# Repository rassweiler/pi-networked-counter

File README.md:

# pi-networked-counter
Network attached counter using Pi5, python, pyqt6, and sqlite

## Dev Setup (Linux)

- clone repository:
```
git clone https://github.com/rassweiler/pi-networked-counter.git && cd pi-networked-counter
```

- Setup python environment:
```
python3 -m venv venv

source venv/bin/activate

pip3 install gpiozero lgpio msal msal_extensions python-dotenv pygobject
```

- Install optional packages:
```
sudo apt install qtcreator sqlitebrowser
```

## Device Setup (Pi5+)

### Base Version Part List
- 1 [Raspberry Pi 5+](https://www.canakit.com/raspberry-pi-5-8gb.html?cid=CAD&src=raspberrypi)
- 1 [Raspberry Pi 5+ Power Supply](https://www.canakit.com/official-raspberry-pi-5-power-supply-27w-usb-c.html?defpid=4863)
- 1 [Micro SSD](https://www.amazon.ca/Samsung-Memory-Adapter-Limited-Warranty/dp/B09FFD6R2B/)
- 1 [Raspberry Pi 7" screen](https://www.canakit.com/raspberry-pi-lcd-display-touchscreen.html)
- 1 [Pi5 Diplay adapter cable](https://www.canakit.com/raspberry-pi-5-display-cable.html)
- 2 [Harting Cables](https://www.digikey.ca/en/products/detail/harting/21350102507010/16669171)
- 2 [M12 AMP Connector Male](https://www.digikey.ca/en/products/detail/te-connectivity-amp-connectors/T4171010005-001/7927449)
- 2 [M12 AMP Connector Female](https://www.digikey.ca/en/products/detail/te-connectivity-amp-connectors/T4171110005-001/7221411)
- 1 [Pack of jumper pin connectors](https://www.amazon.ca/Elegoo-120pcs-Multicolored-Breadboard-arduino/dp/B01EV70C78/)
- 1 [Roll of PETG filament](https://www.prusa3d.com/product/prusament-petg-anthracite-grey-1kg/)
- 2 [IR Emitter/ Receiver 5mm 3.3v](https://www.adafruit.com/product/2168#technical-details)
- 1 [Ethernet Keystone Inline](https://www.amazon.ca/5PACK-CAT6-Keystone-Inline-Coupler-White/dp/B0116T7XMQ/)
- 1 [Ethernet Patch Cable](https://www.amazon.ca/Cat-Ethernet-Cable-0-5ft-Pack/dp/B0CMQG7GS1)
- 1 [USB C Keystone Jack Adapter USB 3.1](https://www.amazon.ca/AAOTOKK-Keystone-Adapter-Type-C-Coupler/dp/B07Z947FRN)
- 1 [USB C patch cable](https://www.amazon.ca/Silkland-Charging-Compatible-MacBook-Samsung/dp/B0CQ4SX256)
- 1 [USB A Keystone Jack Cable](https://www.amazon.ca/Keystone-Haokiang-Adapters-Connector-Cable-20CM/dp/B07JFRLLQF)
- 1 [22awg Wire 2 Conductor 25ft](https://www.digikey.ca/en/products/detail/prysmian/C6348A-46-10/2761061)
- 1 [Rugged Metal Pushbutton - 16mm White Momentary](https://www.adafruit.com/product/558)
- 2 [Wire Connector Pack](https://www.amazon.ca/Connector-Solderless-Connectors-Stripping-Electrical/dp/B08929GXGK)
- 1 [GPIO Ribbon Cable](https://www.adafruit.com/product/1988)
- 1 [GPIO Header](https://www.pishop.ca/product/40-pin-gpio-connector-header/)

### Stacklight Version Part List
- 1 [DC Power Panel Jack](https://www.amazon.ca/DIYhz-Socket-Female-Mounting-Connector/dp/B079D6P26P)
- 1 [DC Power Supply](https://www.amazon.ca/ALITOVE-Adapter-Converter-100-240V-5-5x2-1mm/dp/B01GEA8PQA)
- 1 [Through-Hole Resistors - 1K ohm 5% 1/4W](https://www.adafruit.com/product/4294)
- 1 [Through-Hole Resistors - 220 ohm 5% 1/4W](https://www.adafruit.com/product/2780)
- 1 [AQY210EH SSR](https://www.digikey.ca/en/products/detail/panasonic-electric-works/AQY210EH/513082)
- 1 [Tower Light - Red Yellow Green Alert Light](https://www.adafruit.com/product/2993#technical-details)
- 1 [Tiny Premium Breadboard](https://www.adafruit.com/product/65#description)

### Optional Parts
- 1 [Pi5 POE Hat](https://www.pishop.ca/product/power-over-ethernet-hat-f-for-raspberry-pi-5-cooling-fan-802-3af-at/)

### Pi Software

- Update system
```
sudo apt update && sudo apt upgrade
```

- Install packages
```
sudo apt install < .packages
```

- Disable sudo NOPASSWD:
```
sudo nano /etc/sudoers.d/010_pi-nopasswd

remove NOPASSWD:
```

- Enable sudo logging:
```
sudo visudo

Insert:

Defaults    logfile=/var/log/sudo
```

- Harden ssh config:
```
sudo nano /etc/ssh/sshd_config

PermitRootLogin prohibit-password
MaxAuthTries 5
MaxSessions 3
MaxStartups 3:90:15
PasswordAuthentication no
```

- Harden ssh keys:
```
echo -e "# Restrict key exchange, cipher, and MAC algorithms, as per sshaudit.com\n# hardening guide.\n KexAlgorithms sntrup761x25519-sha512,sntrup761x25519-sha512@openssh.com,curve25519-sha256,curve25519-sha256@libssh.org,gss-curve25519-sha256-,diffie-hellman-group16-sha512,gss-group16-sha512-,diffie-hellman-group18-sha512,diffie-hellman-group-exchange-sha256\n\nCiphers chacha20-poly1305@openssh.com,aes256-gcm@openssh.com,aes256-ctr,aes192-ctr,aes128-gcm@openssh.com,aes128-ctr\n\nMACs hmac-sha2-256-etm@openssh.com,hmac-sha2-512-etm@openssh.com,umac-128-etm@openssh.com\n\nHostKeyAlgorithms sk-ssh-ed25519-cert-v01@openssh.com,ssh-ed25519-cert-v01@openssh.com,rsa-sha2-512-cert-v01@openssh.com,rsa-sha2-256-cert-v01@openssh.com,sk-ssh-ed25519@openssh.com,ssh-ed25519,rsa-sha2-512,rsa-sha2-256\n\nRequiredRSASize 3072\n\nCASignatureAlgorithms sk-ssh-ed25519@openssh.com,ssh-ed25519,rsa-sha2-512,rsa-sha2-256\n\nGSSAPIKexAlgorithms gss-curve25519-sha256-,gss-group16-sha512-\n\nHostbasedAcceptedAlgorithms sk-ssh-ed25519-cert-v01@openssh.com,ssh-ed25519-cert-v01@openssh.com,sk-ssh-ed25519@openssh.com,ssh-ed25519,rsa-sha2-512-cert-v01@openssh.com,rsa-sha2-512,rsa-sha2-256-cert-v01@openssh.com,rsa-sha2-256\n\nPubkeyAcceptedAlgorithms sk-ssh-ed25519-cert-v01@openssh.com,ssh-ed25519-cert-v01@openssh.com,sk-ssh-ed25519@openssh.com,ssh-ed25519,rsa-sha2-512-cert-v01@openssh.com,rsa-sha2-512,rsa-sha2-256-cert-v01@openssh.com,rsa-sha2-256\n\n" > /etc/ssh/sshd_config.d/ssh-audit_hardening.conf
```

- Remove avahi:
```
sudo systemctl stop avahi-daemon && sudo systemctl disable avahi-daemon

sudo apt purge avahi-daemon -y
```

- Remove CUPS:
```
sudo systemctl stop cups && sudo systemctl disable cups

sudo apt purge cups -y 
```

- PI configure
Set the locale to UTF-8

- Setup keyring for sharepoint integration
Run seahorse and make sure there is a default keystore

- clone repository to PI:
```
git clone https://github.com/rassweiler/pi-networked-counter.git && cd pi-networked-counter
```

- Copy the desktop file to autostart the app:
```
sudo cp objectcounter.desktop /etc/xdg/autostart/objectcounter.desktop
```

- Add panel icon
```
cp objectcounter.desktop ~/.local/share/applications/
```

Then restart the system to get the app in the menu under other, then right click the app and select add to taskbar

- Setup startup IO for push button
```
echo "dtoverlay=gpio-poweroff,gpiopin=25,active_low" >> /boot/firmware/config.txt
```

### Sharepoint Setup (Optional)

- Add to the `.settup.toml` file your sharepoint access details:
```
[sharepoint]
authority = "https://login.microsoftonline.com/{AID}"
client = "{CID}"
scopes = 'User.ReadBasic.All Files.ReadWrite Sites.ReadWrite.All'
endpoint = "https://graph.microsoft.com/v1.0/me" 
```

- run the `get_token.sh` script once to initialise your sharepoint token, it should provide a link and a key to login using a browser.

### Print Parts

- Print out the [Front case](./Models/Exports/NetworkCounter_Case_Front_Print.3mf) section (Should contain the screen brackets as well)
- Print out the [Rear case](./Models/Exports/NetworkCounter_Case_Back_Print.3mf) section
- Print out the [Sensor case](./Models/Exports/NetworkCounter_SensorCase_Front_Print.3mf) sections
- Print any required brackets/stands

### Prepare Sensors

- Connect both power wires together from the IR emitter and receiver
- Connect both ground wires together from the IR emitter and receiver
- Solder the M12 AMP Connector Male to the sensors following the pinout below

### Sensor Pinout To Cable

- Pin 1 (Brown): 3.3V 
- Pin 2 (White): Unused 
- Pin 3 (Blue): Emitter signal (Yellow) 
- Pin 4 (Black): Ground 
- Pin 5 (Gray): Unused

### Lightstack Pinout

- Cable Brown: 12V 
- Cable Green: Green LED 
- Cable Yellow: Yellow LED 
- Cable Red: Red LED 

### Pi5 Wiring 

- Pin 1 (3.3V): To infeed sensor pin 1
- Pin 2 (5V): To Display pin 5 (5V)
- Pin 6 (GND): To Display pin 1 (GND)
- Pin 9 (GND): To infeed sensor pin 4
- Pin 11: To infeed sensor pin 3
- Pin 13: To stack light green wire
- Pin 14 (GND): To outfeed sensor pin 4
- Pin 15: To stack light yellow wire
- Pin 16: To outfeed sensor pin 3
- Pin 17: (3.3V): To outfeed sensor pin 1
- Pin 18: To stack light red wire
- Pin 22: To power led +
- Pin 25 (GND): To dev board for ground
- Pin 30 (GND): To power led -

### Assembly Schematic
The Pi5 board is not entirely accurate, the J2 and J8 pins are proper however.

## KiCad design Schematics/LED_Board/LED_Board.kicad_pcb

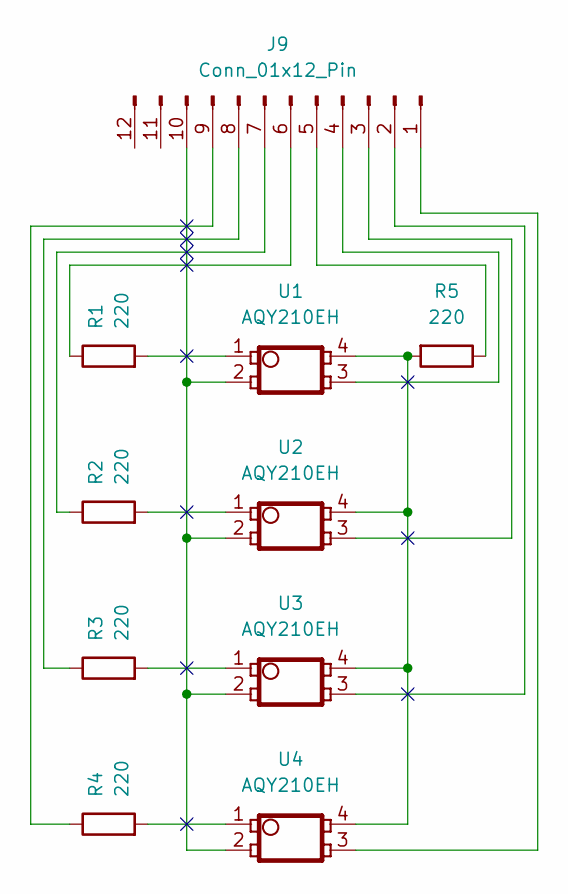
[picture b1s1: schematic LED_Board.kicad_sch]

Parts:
J9: Conn_01x12_Pin; PinHeader_1x12_P2.54mm_Vertical
R1, R2, R3, R4, R5: 220; R_Axial_DIN0204_L3.6mm_D1.6mm_P5.08mm_Horizontal
U1, U2, U3, U4: AQY210EH; Panasonic_AQY210EH

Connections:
unnamed: J9.1, U4.3
unnamed: J9.2, U3.3
unnamed: J9.3, U2.3
unnamed: J9.4, U1.3
unnamed: J9.5, R5.1
unnamed: J9.6, R1.1
unnamed: J9.7, R2.1
unnamed: J9.8, R3.1
unnamed: J9.9, R4.1
unnamed: J9.10, U1.2, U2.2, U3.2, U4.2
unnamed: R1.2, U1.1
unnamed: R2.2, U2.1
unnamed: R3.2, U3.1
unnamed: R4.2, U4.1
unnamed: R5.2, U1.4, U2.4, U3.4, U4.4

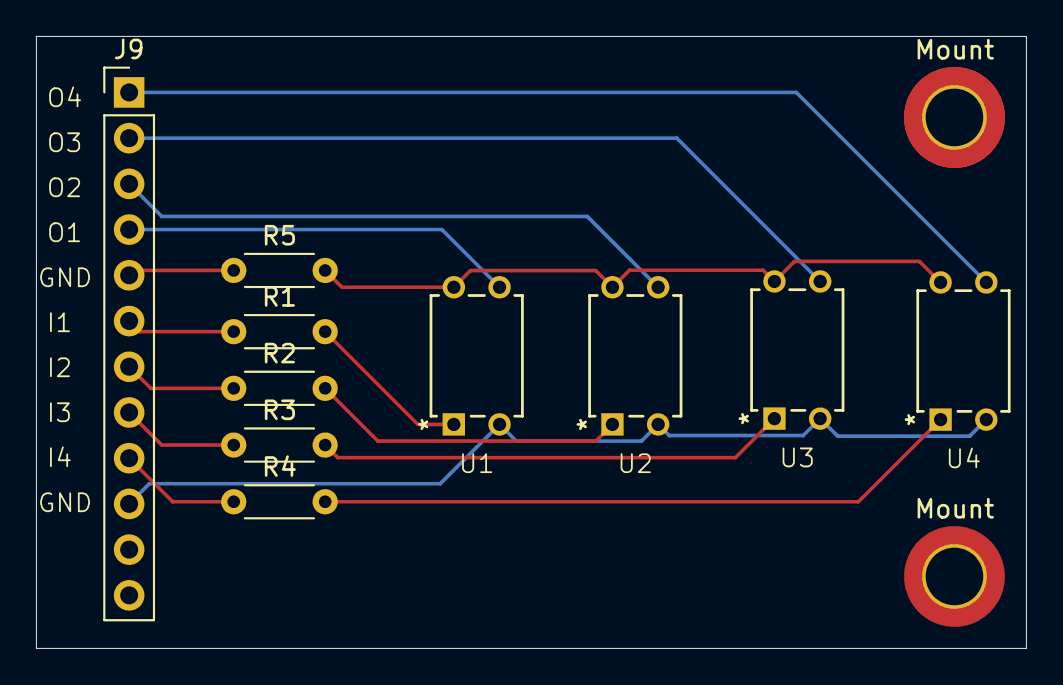
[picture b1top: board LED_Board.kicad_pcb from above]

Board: 2 copper layers, 55.0 x 34.0 mm, 12 parts (0 on the bottom side), 15 nets.

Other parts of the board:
Mount: MountingHole_3.2mm_M3_DIN965_Pad_TopBottom
Mount#2: MountingHole_3.2mm_M3_DIN965_Pad_TopBottom

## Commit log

2024-07-27 Initial commit
    Initial setup scripts and gitignore
    IO test for pi distance sensors
    Initial qt display with sqlite backend
2024-07-29 Setup debug page
    - Change setting page to debug page
    - Add monitors for raw sensor data
    - Add toggles for various settings
2024-07-29 Setup distance sensors
    - Move sensor variables into class
    - Setup base setting options
    - Setup threads and timer for sensor checks
2024-07-29 set base size
    match pi display size
    update permissions
    setup icons and install steps
2024-07-30 Add images and models
    - Add models for case
    - Add iamges for readme
2024-08-02 update models
    - update main assembly
    - add sensor case models
    - update readme
2024-09-13 update models
    - update main assembly
    - add sensor case models
    - update readme
    update form
    - clean up ui
    - add section for target count
2024-12-19 UI Update
2024-12-19 Add launchers
2024-12-19 Update start script
2024-12-19 Add sharepoint exporting, cleanup code
2024-12-20 Add clear database button, prevent oversized ui
2025-04-04 Model updates
2025-04-04 Stack light logic and UI
2025-04-04 Sharepoint export error logging
2025-04-11 Update documentation
2025-04-11 Add UI element for IO troubleshooting and count value on pace screen
2025-04-15 Fix permissions
2025-09-25 Adds typing, adds ui option for single file export, adds setup for double mode
2025-10-09 Cleanup setup
2026-03-07 Update setup and diagrams
